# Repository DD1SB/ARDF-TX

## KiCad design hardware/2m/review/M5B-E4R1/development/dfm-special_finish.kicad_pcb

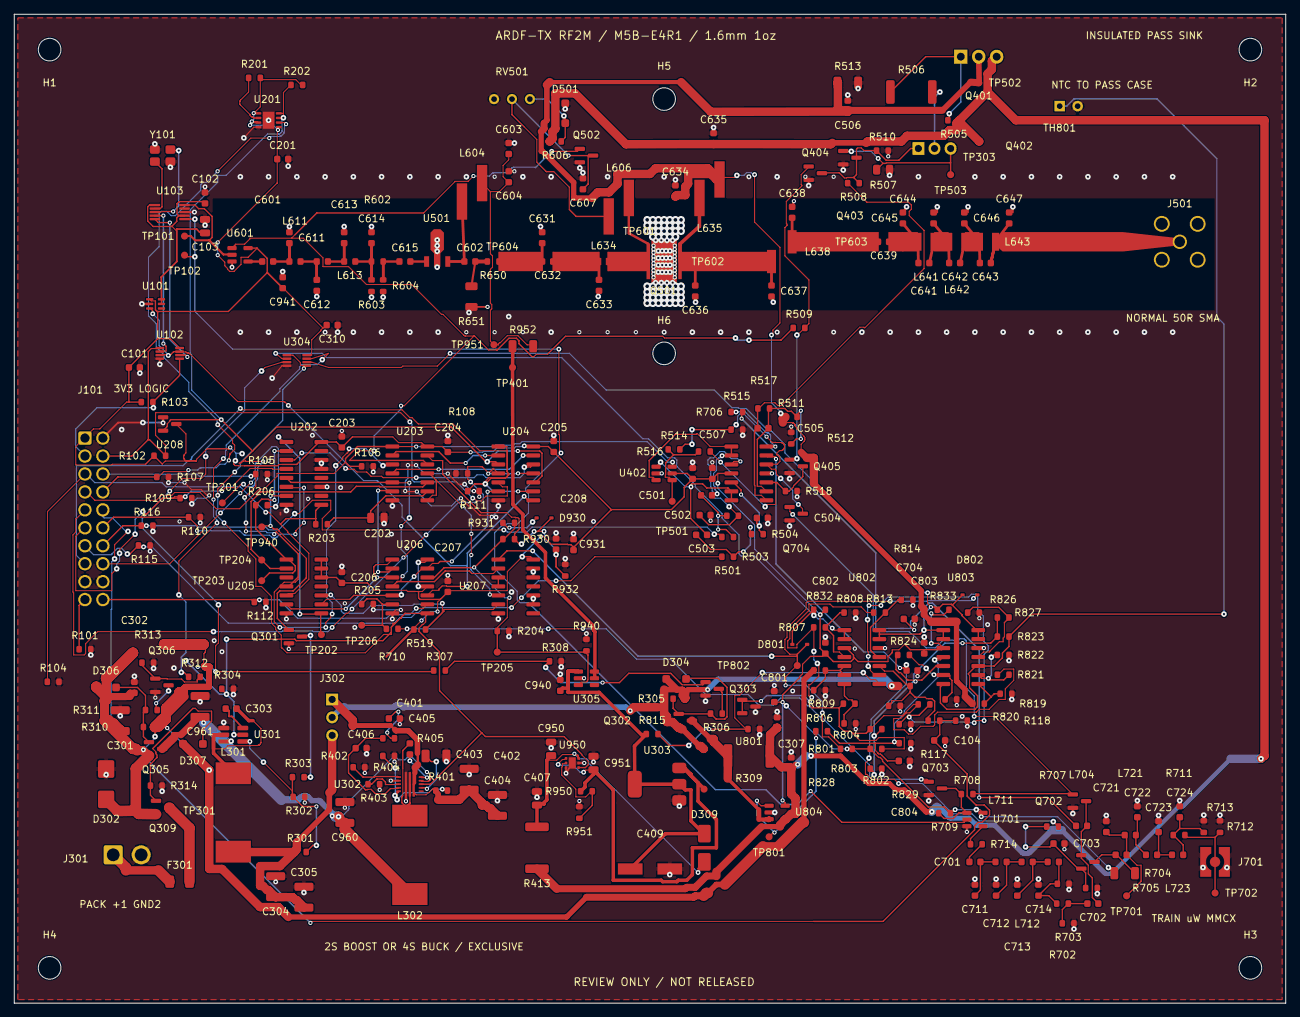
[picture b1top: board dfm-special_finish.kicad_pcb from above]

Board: 2 copper layers, 180.0 x 140.0 mm, 326 parts (0 on the bottom side), 169 nets.

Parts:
C101, C102, C201, C203, C204, C205, C206, C207, C208, C302, C303, C306, C307, C310, C401, C506, C507, C508, C603, C607, C801, C802, C803, C931, C940, C941: 100n; C_0603_1608Metric_E3
C103, C202, C407: 1u; C_0805_2012Metric_E3
C104, C602, C604, C615, C703, C705, C706, C804: 1n; C_0603_1608Metric_E3
C301: 10u; C_1210_3225Metric_E3
C304, C305, C403, C404, C960, C961: 22u; C_1210_3225Metric_E3
C402: 4.7u; C_1206_3216Metric_E3
C405, C501, C502, C503, C504, C505: 4.7n; C_0603_1608Metric_E3
C406, C601, C637, C701, C702, C704: 100p; C_0603_1608Metric_E3
C409: 150u; CP_Panasonic_OSCON_C10
C611, C614, C711, C714, C721, C724: 8.2p; C_0603_1608Metric_E3
C612, C613, C636, C712, C713, C722, C723: 33p; C_0603_1608Metric_E3
C631, C633, C644, C646: 22p; C_0603_1608Metric_E3
C632, C634, C639: 330p; C_0603_1608Metric_E3
C635: 1u; C_0603_1608Metric_E3
C638: 39p; C_0603_1608Metric_E3
C641: 3.3p; C_0603_1608Metric_E3
C642: 18p; C_0603_1608Metric_E3
C643: 12p; C_0603_1608Metric_E3
C645: 27p; C_0603_1608Metric_E3
C647: 15p; C_0603_1608Metric_E3
C950, C951: 4.7u; C_0805_2012Metric_E3
D302: SMBJ18A; D_SMB_E3
D304: 10V gate clamp; D_SOD-123F_E3
D306: 10V input gate clamp; D_SOD-123F_E3
D307: 10V reverse-FET gate clamp; D_SOD-123F_E3
D309: SS14 LDO reverse discharge; D_SMA_E3
D501: 6.2V bias ceiling; D_SOD-123F_E3
D801, D802: BAT54 fault AND; D_SOD-323_E3
D930: BAT54WS; D_SOD-323_E3
F301: 4A fast / qualify I2t; Fuse_1206_3216Metric_E3
H1, H2, H3, H4, H5, H6: MountingHole_3.2mm_M3; MountingHole_3.2mm_M3_E3
J101: Controller 20 pin; WR_BHD_61202021621
J301: Protected pack JST VH; JST_VH_B2P-VH_1x02_P3.96mm_Vertical_E3
J302: Exclusive converter link; PinHeader_1x03_P2.54mm_Vertical_E3
J501: NORMAL 50ohm SMA; SMA_Amphenol_132134_Vertical_E3
J701: TRAIN MMCX 50ohm; WR-MMCX_Wuerth_66012102111404_Vertical_E3
L301: 10u; Bourns_SRP1265A
L302: 4.7u; Bourns_SRP1265A
L604: 150n; Coilcraft_1812SMS_Doc184
L606, L635: 33n; Coilcraft_1812SMS_Doc184
L611, L613, L711, L713, L721, L723: 56n; L_0603_1608Metric_E3
L612, L712, L722: 91n; L_0603_1608Metric_E3
L634: 47n; Coilcraft_0603HC_Doc218
L638: 18.5n; Coilcraft_A05T_Doc107
L641: 39n; Coilcraft_1008CS_Doc101
L642: 22n; Coilcraft_1008CS_Doc101
L643: 27n; Coilcraft_1008CS_Doc101
L704: 180n; L_0603_1608Metric_E3
Q301, Q502: 2N7002; SOT-23_E3
Q302, Q305, Q309: AO3401A; SOT-23_E3
Q303, Q306, Q403, Q404, Q405, Q702, Q703, Q704: MMBT3904,215; SOT-23_E3
Q401: D45H11; TO-220-3_Vertical_E3
Q402: BD139; TO-126-3_Vertical_E3
Q501: PD54008L-E; PD54008L_ST_GDS_5x5
Q701: MMBTH10LT1G; SOT-23_E3
R101: 18.2k; R_0603_1608Metric_E3
R102, R103, R305, R307, R310, R312, R505, R710: 4.7k; R_0603_1608Metric_E3
R104, R105, R106, R107, R108, R109, R110, R111, R112, R115, R116, R118, R204, R205, R304, R308, R313, R402, R510, R518, R932, R940: 100k; R_0603_1608Metric_E3
R117, R206, R306, R311, R508, R516, R606, R707, R709, R826: 1k; R_0603_1608Metric_E3
R201, R202, R203, R302, R314, R405, R501, R502, R503, R504, R509, R512, R515, R706, R708, R804, R806, R808, R810, R812, R814, R816, R818, R820, R822, R823, R825, R827, R832, R833, R930, R951: 10k; R_0603_1608Metric_E3
R301: 116k; R_0603_1608Metric_E3
R303: 46.4k; R_0603_1608Metric_E3
R309: 0.068; R_2512_6332Metric_E3
R401: 634k; R_0603_1608Metric_E3
R403: 150k; R_0603_1608Metric_E3
R404: 340k; R_0603_1608Metric_E3
R413: 4.7; R_2512_6332Metric_E3
R506: 10; R_2512_6332Metric_E3
R507: 8.2; R_0805_2012Metric_E3
R511: 18k; R_0603_1608Metric_E3
R513: 1k; R_1206_3216Metric_E3
R514: 27k; R_0603_1608Metric_E3
R517, R519, R650: 0; R_0603_1608Metric_E3
R602: 71.5; R_0603_1608Metric_E3
R603, R604: 96.5; R_0603_1608Metric_E3
R651: 49.9; R_1206_3216Metric_E3
R702: 680; R_0603_1608Metric_E3
R703: 10; R_0603_1608Metric_E3
R704: 100; R_1206_3216Metric_E3
R705: 47; R_0603_1608Metric_E3
R711: 154; R_0603_1608Metric_E3
R712, R713: 68.1; R_0603_1608Metric_E3
R714: 100; R_0603_1608Metric_E3
R715: 51.1; R_0603_1608Metric_E3
R801: 150; R_0603_1608Metric_E3
R802: 620; R_0603_1608Metric_E3
R803: 470; R_0603_1608Metric_E3
R805: 160k; R_0603_1608Metric_E3
R807: 58.3k; R_0603_1608Metric_E3
R809: 39.2k; R_0603_1608Metric_E3
R811: 120k; R_0603_1608Metric_E3
R813: 20.9k; R_0603_1608Metric_E3
R815: 73.2k; R_0603_1608Metric_E3
R817: 29.4k; R_0603_1608Metric_E3
R819: 110k; R_0603_1608Metric_E3
R821: 26.5k; R_0603_1608Metric_E3
R824: 49.9k; R_0603_1608Metric_E3
R828: 5.11k; R_0603_1608Metric_E3
R829: 4.02k; R_0603_1608Metric_E3
R931: 330; R_0603_1608Metric_E3
R950: 58.2k; R_0603_1608Metric_E3
R952: 0; R_1206_3216Metric_E3
RV501: 10k bias trim; Potentiometer_Bourns_3296W_Vertical_E3
TH801: 10k NTC B3977; NTC_Remote_2Wire
TL603: 50R 6.1129mm; TL50_E3_6p1129mm
TL604: 50R 6.4956mm; TL50_E3_6p4956mm
TL605: 50R 5.691mm; TL50_E3_5p691mm
TL606: 50R 2.1587mm; TL50_E3_2p1587mm
TL607: 50R 10.7933mm; TL50_E3_10p7933mm
TL608: 50R 12.167mm; TL50_E3_12p167mm
TL609: 50R 1.9624mm; TL50_E3_1p9624mm
TP101: CLK_NORMAL; TestPoint_Pad_D1.0mm_E3
TP102: CLK_TRAIN; TestPoint_Pad_D1.0mm_E3
TP201: SAFE_N; TestPoint_Pad_D1.0mm_E3
TP202: CLR_N; TestPoint_Pad_D1.0mm_E3
TP203: VALID_ARM; TestPoint_Pad_D1.0mm_E3
TP204: ARM_DELAY; TestPoint_Pad_D1.0mm_E3
TP205: NORMAL_PERMIT; TestPoint_Pad_D1.0mm_E3
TP206: TRAIN_PERMIT; TestPoint_Pad_D1.0mm_E3
TP301: VIN_PROT; TestPoint_Pad_D1.0mm_E3
TP302: VREG_RAW; TestPoint_Pad_D1.0mm_E3
TP303: VMOD; TestPoint_Pad_D1.0mm_E3
TP401: VDRV_RF; TestPoint_Pad_D1.0mm_E3
TP501: AM_COMMAND; TestPoint_Pad_D1.0mm_E3
TP502: VPA; TestPoint_Pad_D1.0mm_E3
TP503: MOD_E; TestPoint_Pad_D1.0mm_E3
TP601: PA_GATE; Probe_Pad_0p6
TP602: PA_DRAIN; Probe_Pad_0p6
TP603: ST_LPF_IN; Probe_Pad_0p6
TP604: MMIC_AC; Probe_Pad_0p6
TP701: TRAIN_OUT_RAW; TestPoint_Pad_D1.0mm_E3
TP702: TRAIN_RF; TestPoint_Pad_D1.0mm_E3
TP801: ISENSE; TestPoint_Pad_D1.0mm_E3
TP802: POWER_FAULT_N; TestPoint_Pad_D1.0mm_E3
TP940: Captured profile; TestPoint_Pad_D1.0mm_E3
TP950: DRV pre5.456V; TestPoint_Pad_D1.0mm_E3
TP951: MMIC isolated5V; TestPoint_Pad_D1.0mm_E3
U101: TPS22919DCKR; SOT-363_SC-70-6_E3
U102: SN74LVC2G66DCUR; VSSOP-8_2.3x2mm_P0.5mm_E3
U103: Si5351A-B-GT; MSOP-10_3x3mm_P0.5mm_E3
U201: TPS3431SDRBR; VSON-8-1EP_3x3mm_P0.65mm_EP1.65x2.4mm_E3
U202: 74HC174D,653; SOIC-16_3.9x9.9mm_P1.27mm_E3
U203: 74HC14D,653; SOIC-14_3.9x8.7mm_P1.27mm_E3
U204, U206: 74HC11D,653; SOIC-14_3.9x8.7mm_P1.27mm_E3
U205: 74HC21D,653; SOIC-14_3.9x8.7mm_P1.27mm_E3
U207: 74HC32D,653; SOIC-14_3.9x8.7mm_P1.27mm_E3
U208: TLV803EA29DBZR; SOT-23_E3
U301: TPS54302DDCR; SOT-23-6_Handsoldering_E3
U302: TPS611781RNWR; TI_RNW0013A_4222804C
U303: TLV76150DCYR; SOT-223-3_TabPin2_E3
U304: SN74LVC2G08DCUR; VSSOP-8_2.3x2mm_P0.5mm_E3
U305: TPS22810DBVR; SOT-23-6_E3
U401: TLV9004IDR; SOIC-14_3.9x8.7mm_P1.27mm_E3
U402: SN74LVC1G3157DBVR; SOT-23-6_E3
U501: PHA-1+; PHA1_DF782_RevG
U601, U701: SN74LVC1G125DBVR; SOT-23-5_E3
U801: TL431BIDBZR; SOT-23_E3
U802, U803: LM339BDR; SOIC-14_3.9x8.7mm_P1.27mm_E3
U804: INA180A1IDBVR; SOT-23-5_E3
U950: TLV76701DRVR; WSON-6-1EP_2x2mm_P0.65mm_EP1x1.6mm_E3
Y101: 25MHz CL10p 10/10ppm; Crystal_SMD_3225-4Pin_3.2x2.5mm_E3

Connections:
61A: C612.1, L611.2, L612.1
61B: C613.1, L612.2, L613.1
71A: C712.1, L711.2, L712.1
71B: C713.1, L712.2, L713.1
72A: C722.1, L721.2, L722.1
72B: C723.1, L722.2, L723.1
AF_DC: C503.2, U401.6, U401.7, U402.1
AF_F1: C503.1, R503.2, R504.1
AF_F2: C504.1, R504.2, U401.5
AF_PWM: J101.13, R115.1, R503.1
AM_COMMAND: R514.1, R516.1, TP501.1, U402.4
ARM: J101.5, R104.1, R203.1, U202.9, U205.5
ARM_CONTEXT: U202.3, U204.12
ARM_DELAY: TP204.1, U203.10, U205.2
ARM_DELAY_N: U203.8, U203.11, U207.5
ARM_RC: C202.1, R203.2, U203.9
BAT_FUSED: F301.2, Q309.3
BAT_RAW: F301.1, J301.1
BIAS_TOP: D501.1, R606.2, RV501.1
BIAS_WIPER: C607.1, L606.1, Q502.3, RV501.2
BOOST_BST: C401.1, U302.13
BOOST_COMP: C406.1, R405.1, U302.4
BOOST_FB: R401.2, R402.1, U302.5
BOOST_FREQ: R404.1, U302.1
BOOST_ILIM: R403.1, U302.3
BOOST_SW: C401.2, L302.2, U302.7
BOOST_VCC: C402.1, U302.10
BOOT4S: C303.1, U301.6
CLEAR_A: U204.6, U205.9, U206.5, U206.13
CLK_NORMAL: TP101.1, U103.10, U601.2
CLK_TRAIN: TP102.1, U103.6, U701.2
CLR_N: TP202.1, U202.1, U205.8
COMP_C: C405.1, R405.2
CONV_EN: R304.1, U206.8, U301.5, U302.11, U304.1, U304.5, U950.4
CWD: R201.1, U201.2
DRIVER_IN: C615.2, U501.1
DRIVER_PAD: C615.1, R602.2, R604.1
DRV_OV_REF: R817.2, R818.1, U802.9
DRV_PRE_FB: R950.2, R951.1, U950.2
DRV_S: R815.2, R816.1, U802.8
FAULT_N: J101.16, R206.2
FB4S: R301.2, R302.1, R303.1, U301.4
FB4S_SWITCH: Q301.3, R303.2
GND: C101.2, C102.2, C103.2, C104.2, C201.2, C202.2, C203.2, C204.2, C205.2, C206.2, C207.2, C208.2, C301.2, C302.2, C304.2, C305.2, C306.2, C307.2, C310.2, C402.2, C403.2, C404.2, C405.2, C406.2, C407.2, C409.2, C502.2, C504.2, C506.2, C507.2, C508.2, C603.2, C604.2, C607.2, C611.2, C612.2, C613.2, C614.2, C631.2, C633.2, C634.2, C635.2, C636.2, C637.2, C638.2, C644.2, C645.2, C646.2, C647.2, C703.2, C704.2, C705.2, C711.2, C712.2, C713.2, C714.2, C721.2, C722.2, C723.2, C724.2, C801.2, C802.2, C803.2, C804.2, C931.2, C940.2, C941.2, C950.2, C951.2, C960.2, C961.2, D302.2, D501.2, J101.2, J101.17, J101.18, J301.2, J501.2, J701.2, Q301.2, Q303.2, Q306.2, Q403.2, Q404.2, Q405.2, Q501.S, Q502.2, Q702.2, Q703.2, Q704.2, R101.2, R104.2, R105.2, R106.2, R107.2, R108.2, R109.2, R110.2, R111.2, R112.2, R115.2, R116.2, R118.2, R204.2, R205.2, R302.2, R304.2, R308.2, R313.2, R314.2, R402.2, R403.2, R404.2, R507.2, R510.2, R512.2, R513.2, R515.2, R518.2, R603.2, R604.2, R651.2, R703.2, R705.2, R712.2, R713.2, R715.2, R803.2, R806.2, R808.2, R810.2, R812.2, R814.2, R816.2, R818.2, R820.2, R822.2, R825.2, R827.2, R829.2, R932.2, R940.2, R951.2, RV501.3, TH801.2, U101.2, U102.4, U103.8, U201.4, U201.9, U202.8, U202.11, U202.13, U202.14, U203.7, U204.7, U205.7, U206.7, U207.7, U207.9, U207.10, U207.12, U207.13, U208.1, U301.1, U302.2, U302.6, U303.1, U304.4, U305.2, U401.11, U402.2, U501.2, U501.4, U601.3, U701.3, U801.3, U802.12, U803.12, U804.2, U950.3, U950.5, U950.7, Y101.2, Y101.4
HARD_OK_N: D802.1, R833.1, U304.6, U802.13, U802.14, U803.1, U803.2, U803.13, U803.14
I2C_SCL: J101.4, R102.2, U102.1, U204.5
I2C_SDA: J101.3, R103.2, U102.5
INPUT_ENABLE_BASE: Q306.1, R312.2, R313.1
INPUT_GATE: D306.2, Q305.1, R310.1, R311.1
INPUT_SINK: Q306.3, R311.2
ISENSE: R828.1, TP801.1, U804.1
ISENSE_F: C804.1, R828.2, R829.1, U803.4
KEY: J101.7, R106.1, U203.1, U402.6
KEY_N: U203.2, U204.2
LEVEL_DC: C501.2, U401.1, U401.2, U402.3
LEVEL_F1: C501.1, R501.2, R502.1
LEVEL_F2: C502.1, R502.2, U401.3
LEVEL_PWM: J101.14, R116.1, R501.1
MMIC_AC: R650.2, TL603.1, TP604.1
MMIC_COUPLED: C602.2, R650.1, R651.1
MMIC_RF_DC: C602.1, L604.2, U501.3
MODULE_ID: J101.19, R101.1
MOD_BASE: Q402.1, Q403.3, Q404.3, R508.2, R510.1
MOD_COMMAND: Q405.3, R516.2, R518.1, U401.10
MOD_DRIVE: C505.1, R508.1, R517.1, U401.8
MOD_E: Q402.3, Q403.1, R507.1, TP503.1
MOD_OFF_BASE: Q404.1, Q405.1, R509.2
MOD_SINK: Q402.2, R506.2
MUTE_N: J101.9, R108.1, U204.4, U204.11
NORMAL_CLOCK_BUF: C601.1, U601.4
NORMAL_ENABLE_BASE: Q303.1, R307.2, R308.1
NORMAL_FAST_OFF: D930.1, R931.1
NORMAL_OFF: Q502.1, R509.1, U203.12, U601.1
NORMAL_PERMIT: R204.1, R930.1, R931.2, R940.1, TP205.1, U206.12, U305.3
NORMAL_Q: U203.6, U206.2
NORMAL_RC: C931.1, D930.2, R930.2, R932.1, U203.13
NORMAL_RF: C643.2, C647.1, J501.1, L643.2
OV_REF: R809.2, R810.1, U802.7
PACK_OK_N: D801.1, R832.1, U304.2, U802.1, U802.2
PACK_RUN: R312.1, U304.7
PASS_BASE: Q401.1, R505.1, R506.1
PATH_Q: U202.5, U203.5, U206.4, U207.2
PATH_TRAIN: J101.11, R109.1, U202.4
PA_DRAIN: L635.2, Q501.D, TL606.1, TP602.1
PA_GATE: L606.2, Q501.G, TL605.2, TP601.1
PA_PREPARE: J101.20, R112.1, U206.9
PA_RAIL_ADC: C104.1, J101.10, R117.2, R118.1
POWER_FAULT_N: D801.2, D802.2, R804.1, TP802.1, U207.1
PREPARE: J101.15, R111.1, U204.1, U204.9
PROFILE_FULL: J101.12, R110.1, U202.6
PROFILE_Q: Q301.1, TP940.1, U202.7
PROGRESS: J101.8, R107.1, U201.6
PWR_OR_TRAIN: U207.3, U207.4
RAIL_RUN: R307.1, U304.3
REG_GATE: D304.2, Q302.1, R305.1, R306.1
REG_OV_REF: R813.2, R814.1, U802.11
REG_SINK: Q303.3, R306.2
REVERSE_GATE: D307.2, Q309.1, R314.1
RUN_HEALTH: R519.2, U205.10, U207.6
SAFE_N: R202.1, TP201.1, U201.7, U201.8, U204.3, U204.10, U208.2
SCL_CLK: U102.2, U103.4
SDA_CLK: U102.6, U103.5
SLOT: J101.6, R105.1, U203.3, U205.4
SLOT_N: U203.4, U204.13
SRC_FILT: C614.1, L613.2, R602.1, R603.1
SRC_ON: U101.3, U102.3, U102.7, U204.8, U206.10
SRC_RF: C601.2, C611.1, L611.1
ST_DC_BLOCK: C639.2, TL609.1
ST_F1: C641.2, C642.1, C645.1, L641.2, L642.1
ST_F2: C642.2, C643.1, C646.1, L642.2, L643.1
ST_IS_A: C631.1, C632.1, TL603.2
ST_IS_B: C632.2, TL604.1
ST_IS_C: C633.1, L634.1, TL604.2
ST_IS_D: L634.2, TL605.1
ST_LPF_IN: C641.1, C644.1, L641.1, TL609.2, TP603.1
ST_O_A: C636.1, TL606.2, TL607.1
ST_O_B: C637.1, L638.1, TL607.2
ST_O_C: C638.1, L638.2, TL608.1
ST_O_D: C639.1, TL608.2
SW4S: C303.2, L301.1, U301.2
TEMP_HIGH: R826.2, R827.1, U803.11
TEMP_LOW: R824.2, R825.1, U803.6
TEMP_S: R823.2, TH801.1, U803.7, U803.10
TRAIN_BASE: C702.2, L704.2, Q701.1, Q702.3
TRAIN_BASE_DRIVE: R706.1, U401.14
TRAIN_BASE_RF: C702.1, R702.2, R703.1
TRAIN_BIAS: C704.1, L704.1, R706.2
TRAIN_CLOCK_BUF: R714.1, U701.4
TRAIN_CLOCK_LIMIT: C701.1, R714.2
TRAIN_COLLECTOR: C706.1, Q701.3, R704.2
TRAIN_COMMAND: Q704.3, R514.2, R515.1, U401.12
TRAIN_EMITTER: C703.1, Q701.2, R705.1, R707.1
TRAIN_EMITTER_DC: C705.1, R707.2, U401.13
TRAIN_FILT: C714.1, L713.2, R702.1, R715.1
TRAIN_INVERT_BASE: Q703.1, R710.2
TRAIN_OFF: Q703.3, R708.1, R709.1, U701.1
TRAIN_OFF_BASE: Q702.1, Q704.1, R708.2
TRAIN_OUT_FILT: C724.1, L723.2, R711.1, R712.1
TRAIN_OUT_RAW: C706.2, C721.1, L721.1, TP701.1
TRAIN_PERMIT: R205.1, R710.1, TP206.1, U206.6
TRAIN_RF: J701.1, R711.2, R713.1, TP702.1
TRAIN_SRC: C701.2, C711.1, L711.1
TX_OK: U205.6, U206.1, U206.3
UV_REF: R807.2, R808.1, U802.4
V3V3: C101.1, C201.1, C203.1, C204.1, C205.1, C206.1, C207.1, C208.1, C310.1, C507.1, C508.1, C801.1, C802.1, C803.1, C941.1, J101.1, R102.1, R103.1, R201.2, R202.2, R519.1, R704.1, R709.2, R801.1, R804.2, R832.2, R833.2, U101.1, U102.8, U201.1, U201.3, U201.5, U202.16, U203.14, U204.14, U205.12, U205.13, U205.14, U206.11, U206.14, U207.14, U208.3, U304.8, U401.4, U402.5, U601.5, U701.5, U802.3, U803.3, U804.5
VALID_ARM: R206.1, TP203.1, U202.2, U205.1
VBAT_S: R805.2, R806.1, U802.5, U802.6
VBOOST: C403.1, C404.1, J302.1, R401.1, U302.8
VBUCK: C304.1, C305.1, J302.3, L301.2, R301.1
VCLK: C102.1, C103.1, U101.5, U101.6, U103.1, U103.7
VDRV_FILTER: C409.1, C940.1, D309.2, R815.1, U303.2, U305.1
VDRV_LDO_IN: C407.1, C950.1, D309.1, R413.2, U950.6
VDRV_MMIC: C603.1, C604.1, L604.1, R952.2, TP951.1
VDRV_PREREG: C951.1, R950.1, TP950.1, U303.3, U950.1
VDRV_RF: R952.1, TP401.1, U305.5, U305.6
VIN_CONV: C960.1, C961.1, L302.1, Q305.3, U301.3, U302.12
VIN_PROT: C301.1, C302.1, D302.1, D306.1, D307.1, Q305.2, Q309.2, R310.2, R805.1, TP301.1
VMOD: C306.1, C307.1, C635.1, Q401.3, R309.2, R413.1, R505.2, R606.1, TP303.1, U804.4
VPA: C506.1, C634.1, L635.1, Q401.2, R511.1, R513.1, R819.1, TP502.1
VPA_FB: C505.2, R511.2, R512.1, R517.2, U401.9
VPA_OV_REF: R821.2, R822.1, U803.9
VPA_S: R819.2, R820.1, U803.8
VREF1V0: R802.2, R803.1, R823.1, R824.1, R826.1, U803.5
VREF2V5: R801.2, R802.1, R807.1, R809.1, R813.1, R817.1, R821.1, U801.1, U801.2
VREG_RAW: D304.1, J302.2, Q302.2, R305.2, R811.1, TP302.1
VREG_S: R117.1, R811.2, R812.1, U802.10
VREG_SWITCH: Q302.3, R309.1, U804.3
XTAL1: U103.2, Y101.1
XTAL2: U103.3, Y101.3
